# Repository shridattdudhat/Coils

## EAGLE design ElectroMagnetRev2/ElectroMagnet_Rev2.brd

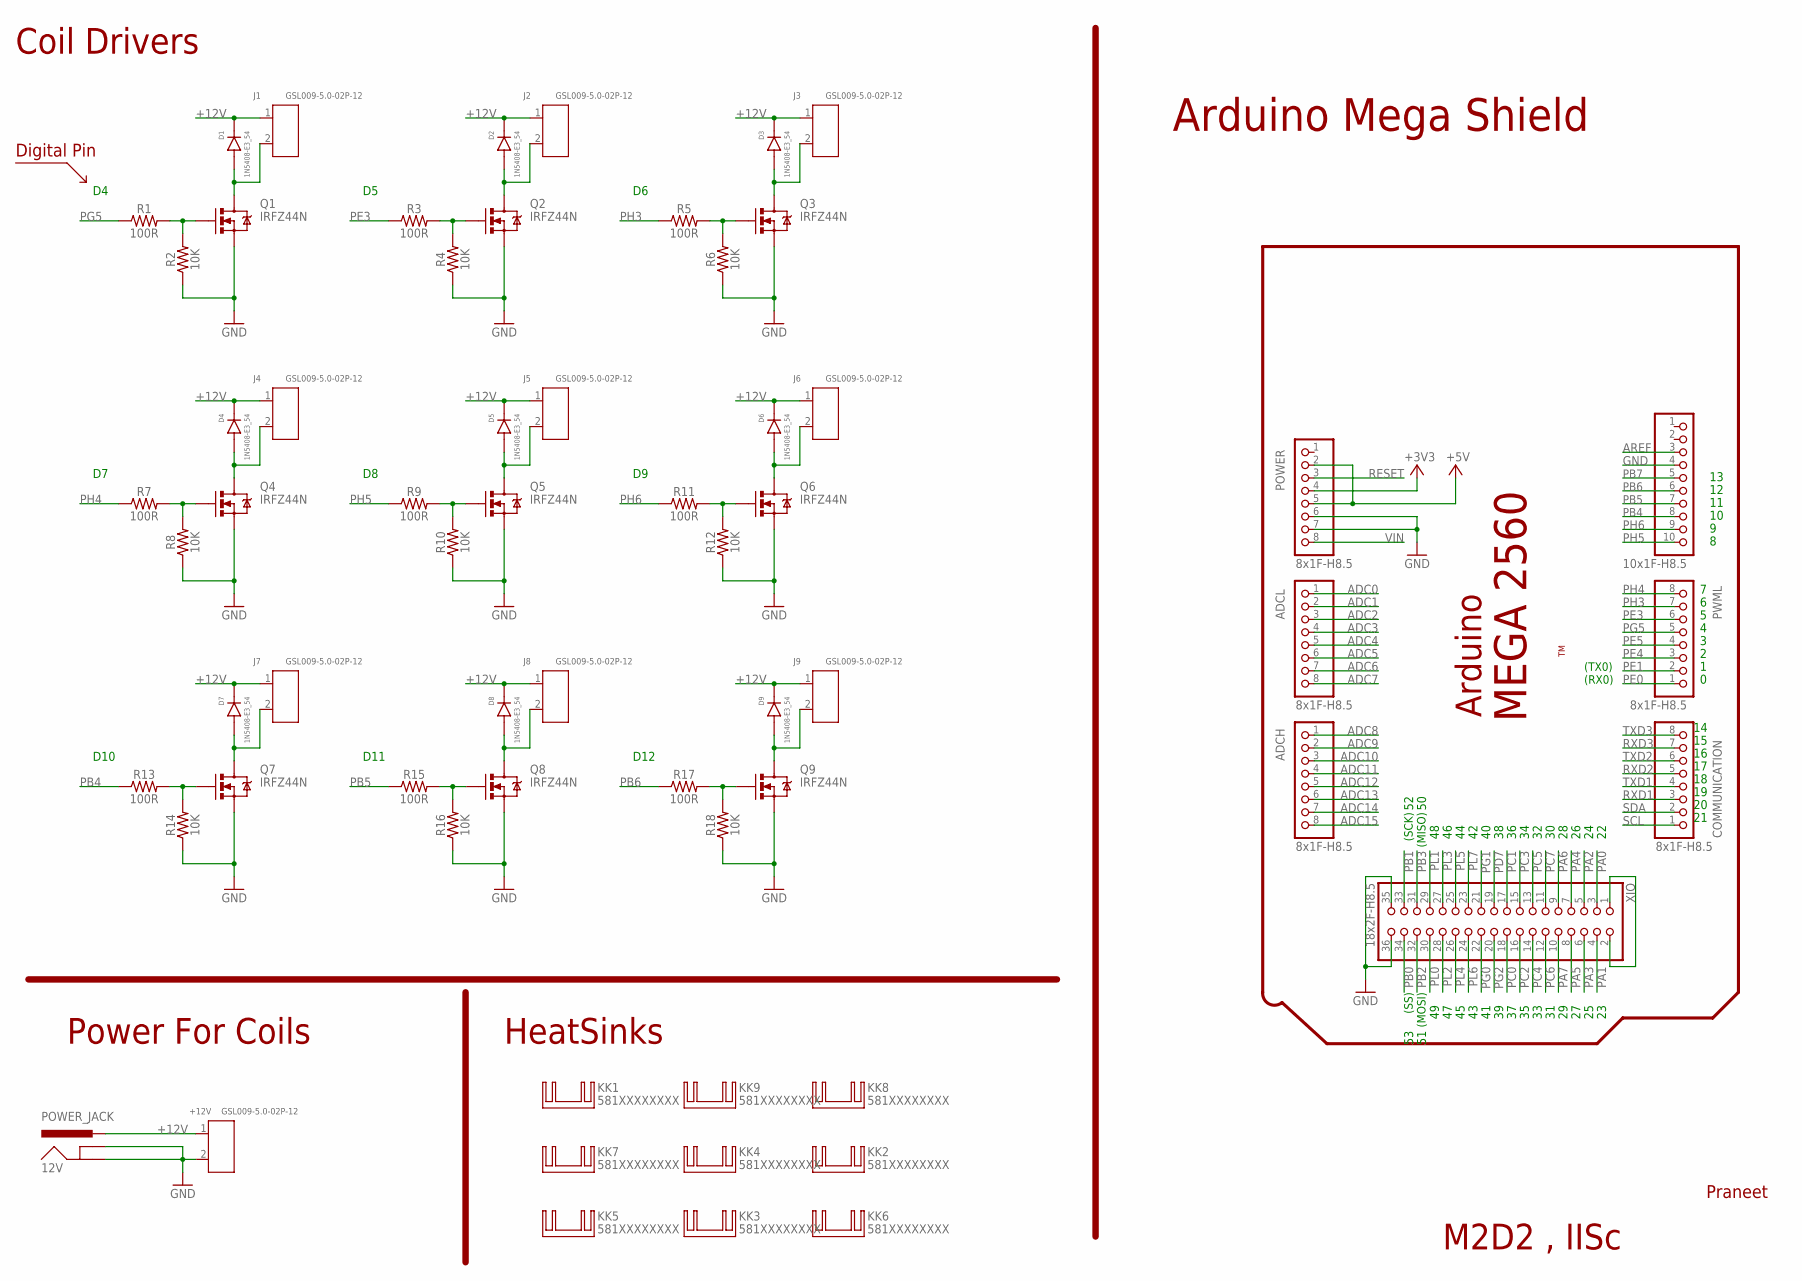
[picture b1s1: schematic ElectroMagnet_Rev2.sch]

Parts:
12V: POWER_JACK; POWER_JACK_PTH
+12V: GSL009-5.0-02P-12; H2-5.0-10.5X8.0MM
ADCH: 8x1F-H8.5; 1X08
ADCL: 8x1F-H8.5; 1X08
COMMUNICATION: 8x1F-H8.5; 1X08
D1, D2, D3, D4, D5, D6, D7, D8, D9: 1N5408-E3_54; DIOAD2855W132L835D505
J1, J2, J3, J4, J5, J6, J7, J8, J9: GSL009-5.0-02P-12; H2-5.0-10.5X8.0MM
JP6: 10x1F-H8.5; 1X10
KK1, KK2, KK3, KK4, KK5, KK6, KK7, KK8, KK9: 581XXXXXXXX
POWER: 8x1F-H8.5; 1X08
PWML: 8x1F-H8.5; 1X08
Q1, Q2, Q3, Q4, Q5, Q6, Q7, Q8, Q9: IRFZ44N; TO-220
R1, R3, R5, R7, R9, R11, R13, R15, R17: 100R; AXIAL-0.3
R2, R4, R6, R8, R10, R12, R14, R16, R18: 10K; AXIAL-0.3
XIO: 18x2F-H8.5; 2X18

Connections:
+3V3: POWER.4
+5V: POWER.2, POWER.5
+12V: 12V.PWR, +12V.1, D1.1 (K), D2.1 (K), D3.1 (K), D4.1 (K), D5.1 (K), D6.1 (K), D7.1 (K), D8.1 (K), D9.1 (K), J1.1, J2.1, J3.1, J4.1, J5.1, J6.1, J7.1, J8.1, J9.1
ADC0: ADCL.1
ADC1: ADCL.2
ADC2: ADCL.3
ADC3: ADCL.4
ADC4: ADCL.5
ADC5: ADCL.6
ADC6: ADCL.7
ADC7: ADCL.8
ADC8: ADCH.1
ADC9: ADCH.2
ADC10: ADCH.3
ADC11: ADCH.4
ADC12: ADCH.5
ADC13: ADCH.6
ADC14: ADCH.7
ADC15: ADCH.8
AREF: JP6.3
GND: 12V.GND, 12V.GNDBREAK, +12V.2, JP6.4, POWER.6, POWER.7, Q1.3 (S), Q2.3 (S), Q3.3 (S), Q4.3 (S), Q5.3 (S), Q6.3 (S), Q7.3 (S), Q8.3 (S), Q9.3 (S), R2.P$1 (1), R4.P$1 (1), R6.P$1 (1), R8.P$1 (1), R10.P$1 (1), R12.P$1 (1), R14.P$1 (1), R16.P$1 (1), R18.P$1 (1), XIO.35, XIO.36
unnamed: XIO.1, XIO.2
unnamed: D1.2 (A), J1.2, Q1.2 (D)
unnamed: Q1.1 (G), R1.P$2 (2), R2.P$2 (2)
unnamed: D2.2 (A), J2.2, Q2.2 (D)
unnamed: Q2.1 (G), R3.P$2 (2), R4.P$2 (2)
unnamed: D3.2 (A), J3.2, Q3.2 (D)
unnamed: Q3.1 (G), R5.P$2 (2), R6.P$2 (2)
unnamed: D4.2 (A), J4.2, Q4.2 (D)
unnamed: Q4.1 (G), R7.P$2 (2), R8.P$2 (2)
unnamed: D5.2 (A), J5.2, Q5.2 (D)
unnamed: Q5.1 (G), R9.P$2 (2), R10.P$2 (2)
unnamed: D6.2 (A), J6.2, Q6.2 (D)
unnamed: Q6.1 (G), R11.P$2 (2), R12.P$2 (2)
unnamed: D7.2 (A), J7.2, Q7.2 (D)
unnamed: Q7.1 (G), R13.P$2 (2), R14.P$2 (2)
unnamed: D8.2 (A), J8.2, Q8.2 (D)
unnamed: Q8.1 (G), R15.P$2 (2), R16.P$2 (2)
unnamed: D9.2 (A), J9.2, Q9.2 (D)
unnamed: Q9.1 (G), R17.P$2 (2), R18.P$2 (2)
PA0: XIO.3
PA1: XIO.4
PA2: XIO.5
PA3: XIO.6
PA4: XIO.7
PA5: XIO.8
PA6: XIO.9
PA7: XIO.10
PB0: XIO.34
PB1: XIO.33
PB2: XIO.32
PB3: XIO.31
PB4: JP6.8, R13.P$1 (1)
PB5: JP6.7, R15.P$1 (1)
PB6: JP6.6, R17.P$1 (1)
PB7: JP6.5
PC0: XIO.18
PC1: XIO.17
PC2: XIO.16
PC3: XIO.15
PC4: XIO.14
PC5: XIO.13
PC6: XIO.12
PC7: XIO.11
PD7: XIO.19
PE0: PWML.1
PE1: PWML.2
PE3: PWML.6, R3.P$1 (1)
PE4: PWML.3
PE5: PWML.4
PG0: XIO.22
PG1: XIO.21
PG2: XIO.20
PG5: PWML.5, R1.P$1 (1)
PH3: PWML.7, R5.P$1 (1)
PH4: PWML.8, R7.P$1 (1)
PH5: JP6.10, R9.P$1 (1)
PH6: JP6.9, R11.P$1 (1)
PL0: XIO.30
PL1: XIO.29
PL2: XIO.28
PL3: XIO.27
PL4: XIO.26
PL5: XIO.25
PL6: XIO.24
PL7: XIO.23
RESET: POWER.3
RXD1: COMMUNICATION.3
RXD2: COMMUNICATION.5
RXD3: COMMUNICATION.7
SCL: COMMUNICATION.1
SDA: COMMUNICATION.2
TXD1: COMMUNICATION.4
TXD2: COMMUNICATION.6
TXD3: COMMUNICATION.8
VIN: POWER.8

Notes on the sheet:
(TX0)
(RX0)
(SS)
(MOSI)
(SCK)
(MISO)
D10
D11
D12
Arduino
MEGA 2560
M2D2 , IISc
Praneet
Arduino Mega Shield
Coil Drivers
Digital Pin
Power For Coils
HeatSinks

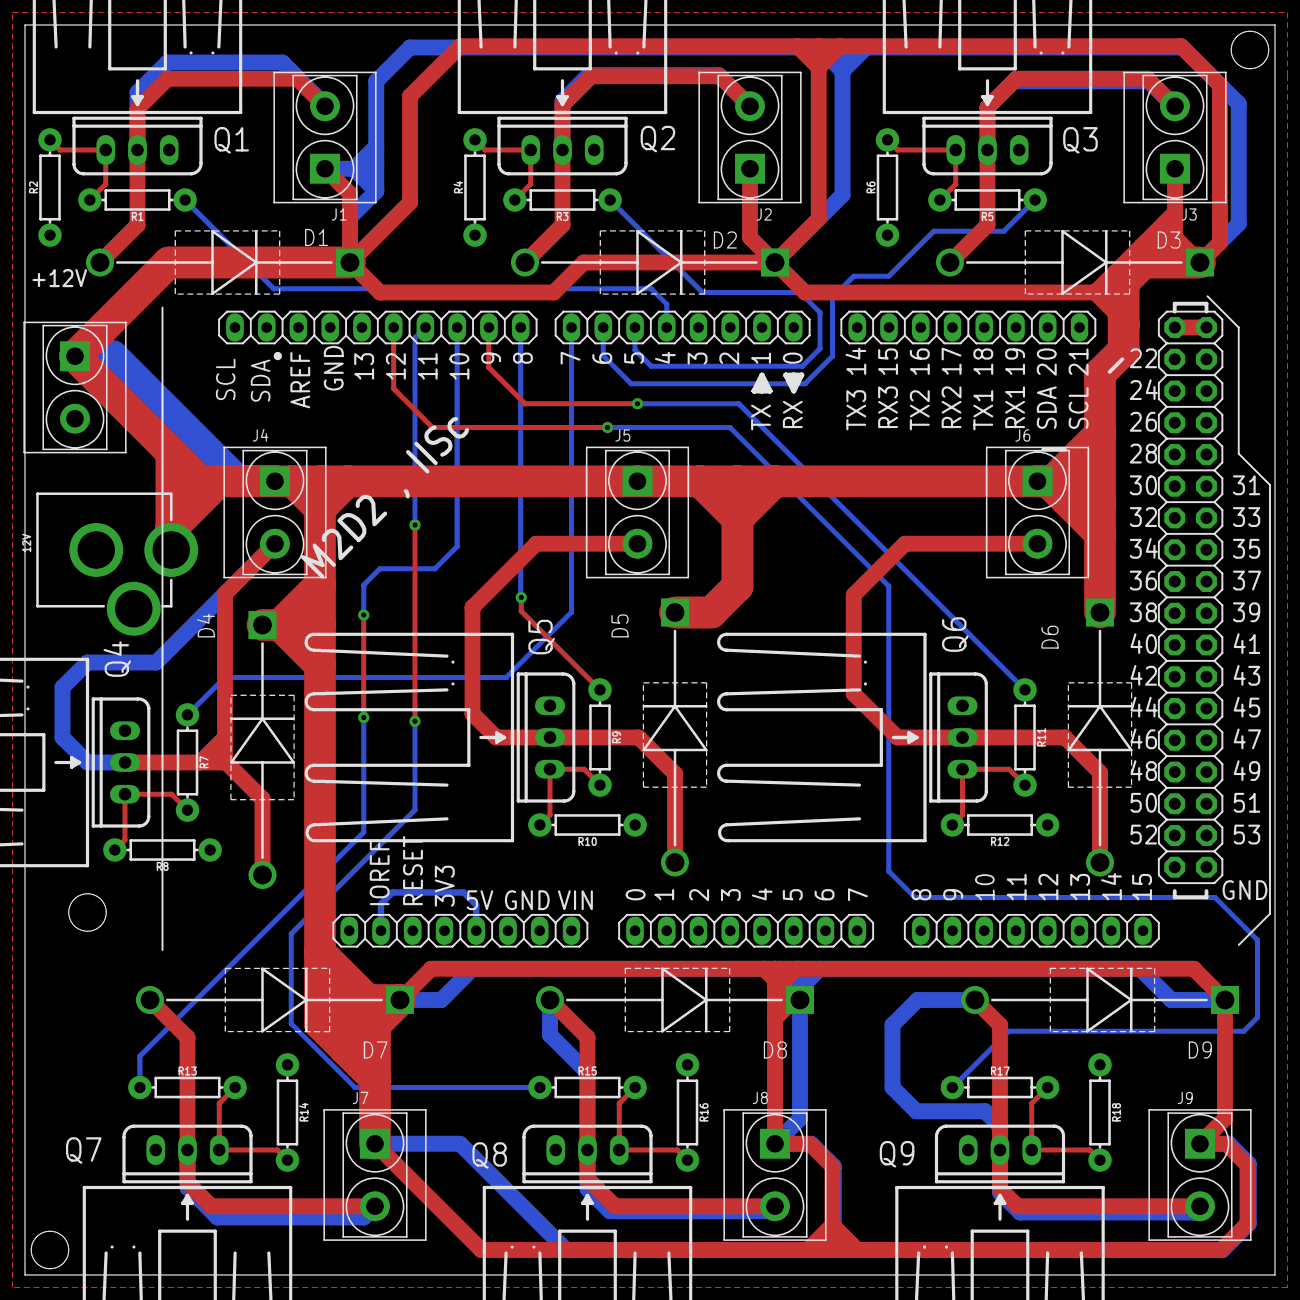
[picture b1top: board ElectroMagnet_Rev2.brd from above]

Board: 2 copper layers, 100.0 x 100.0 mm, 63 parts (0 on the bottom side), 31 nets.

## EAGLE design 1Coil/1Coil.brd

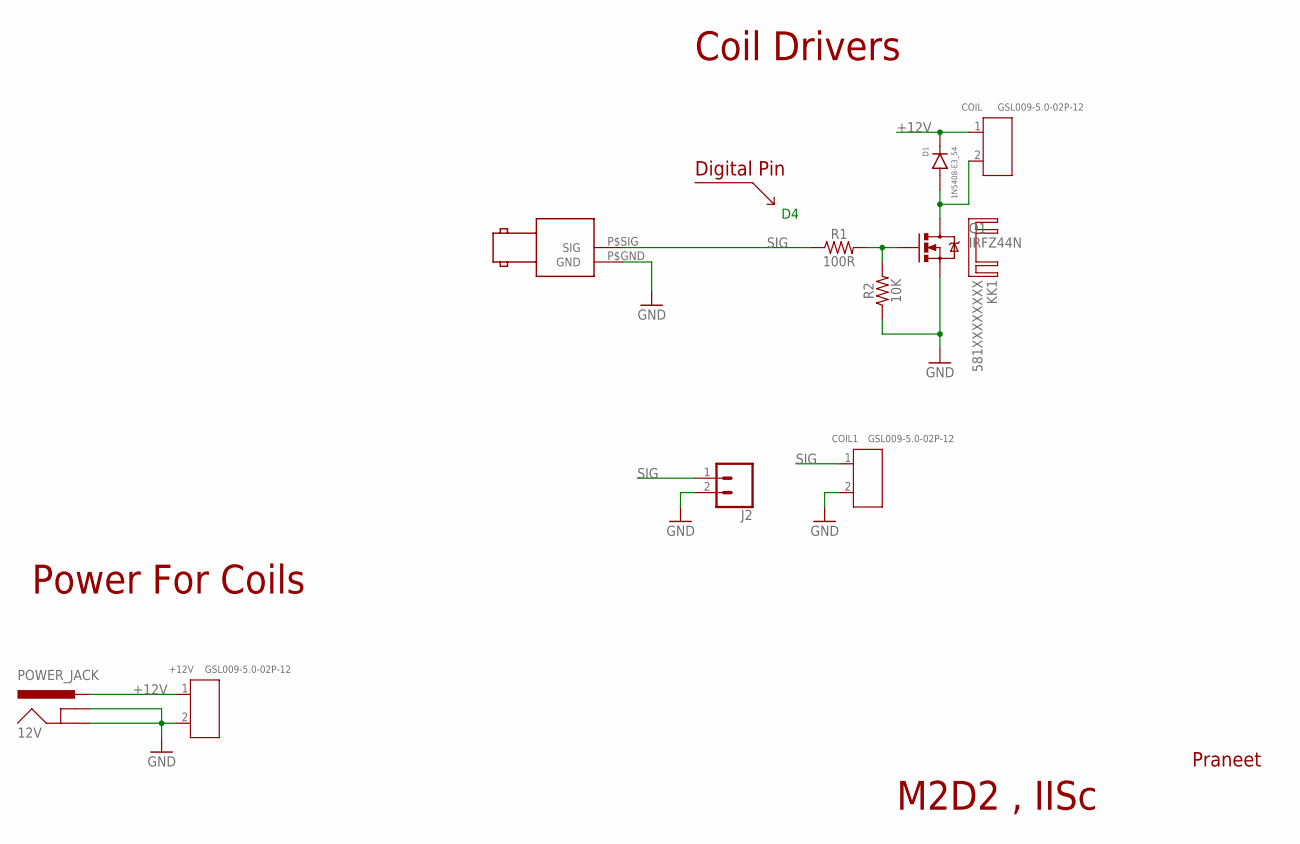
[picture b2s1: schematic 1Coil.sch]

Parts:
12V: POWER_JACK; POWER_JACK_PTH
+12V: GSL009-5.0-02P-12; H2-5.0-10.5X8.0MM
BNC: BNC_RIGHT_ANGLE
COIL, COIL1: GSL009-5.0-02P-12; H2-5.0-10.5X8.0MM
D1: 1N5408-E3_54; DIOAD2855W132L835D505
J2: CONN_02POLAR; MOLEX-1X2
KK1: 581XXXXXXXX
Q1: IRFZ44N; TO-220
R1: 100R; AXIAL-0.3
R2: 10K; AXIAL-0.3

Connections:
+12V: 12V.PWR, +12V.1, COIL.1, D1.1 (K)
GND: 12V.GND, 12V.GNDBREAK, +12V.2, BNC.P$GND (GND), COIL1.2, J2.2, Q1.3 (S), R2.P$1 (1)
unnamed: COIL.2, D1.2 (A), Q1.2 (D)
unnamed: Q1.1 (G), R1.P$2 (2), R2.P$2 (2)
SIG: BNC.P$SIG (SIG), COIL1.1, J2.1, R1.P$1 (1)

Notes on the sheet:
M2D2 , IISc
Praneet
Coil Drivers
Digital Pin
Power For Coils

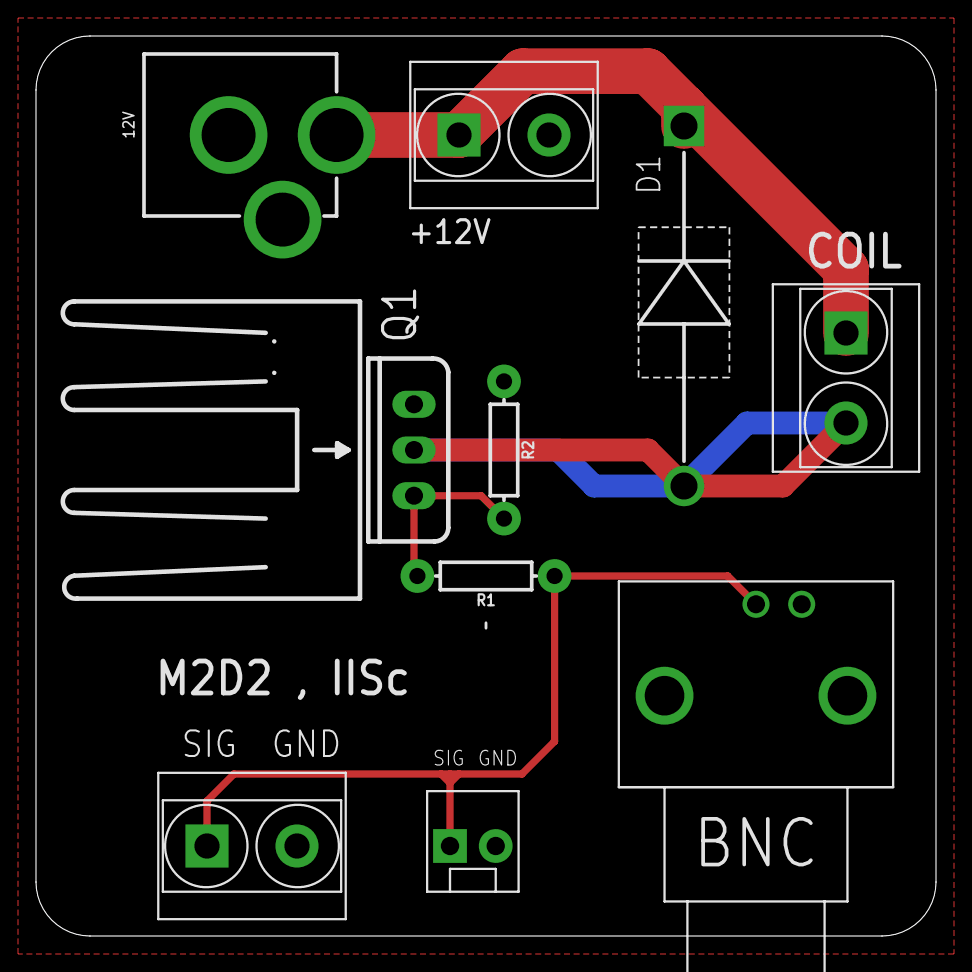
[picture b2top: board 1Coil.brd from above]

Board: 2 copper layers, 50.0 x 50.0 mm, 11 parts (0 on the bottom side), 5 nets.

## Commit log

2019-09-15 ini commit

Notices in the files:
parts and their libraries:
SparkFun-Resistors: Licensing: Creative Commons ShareAlike 4.0 International - https://creativecommons.org/licenses/by-sa/4.0
